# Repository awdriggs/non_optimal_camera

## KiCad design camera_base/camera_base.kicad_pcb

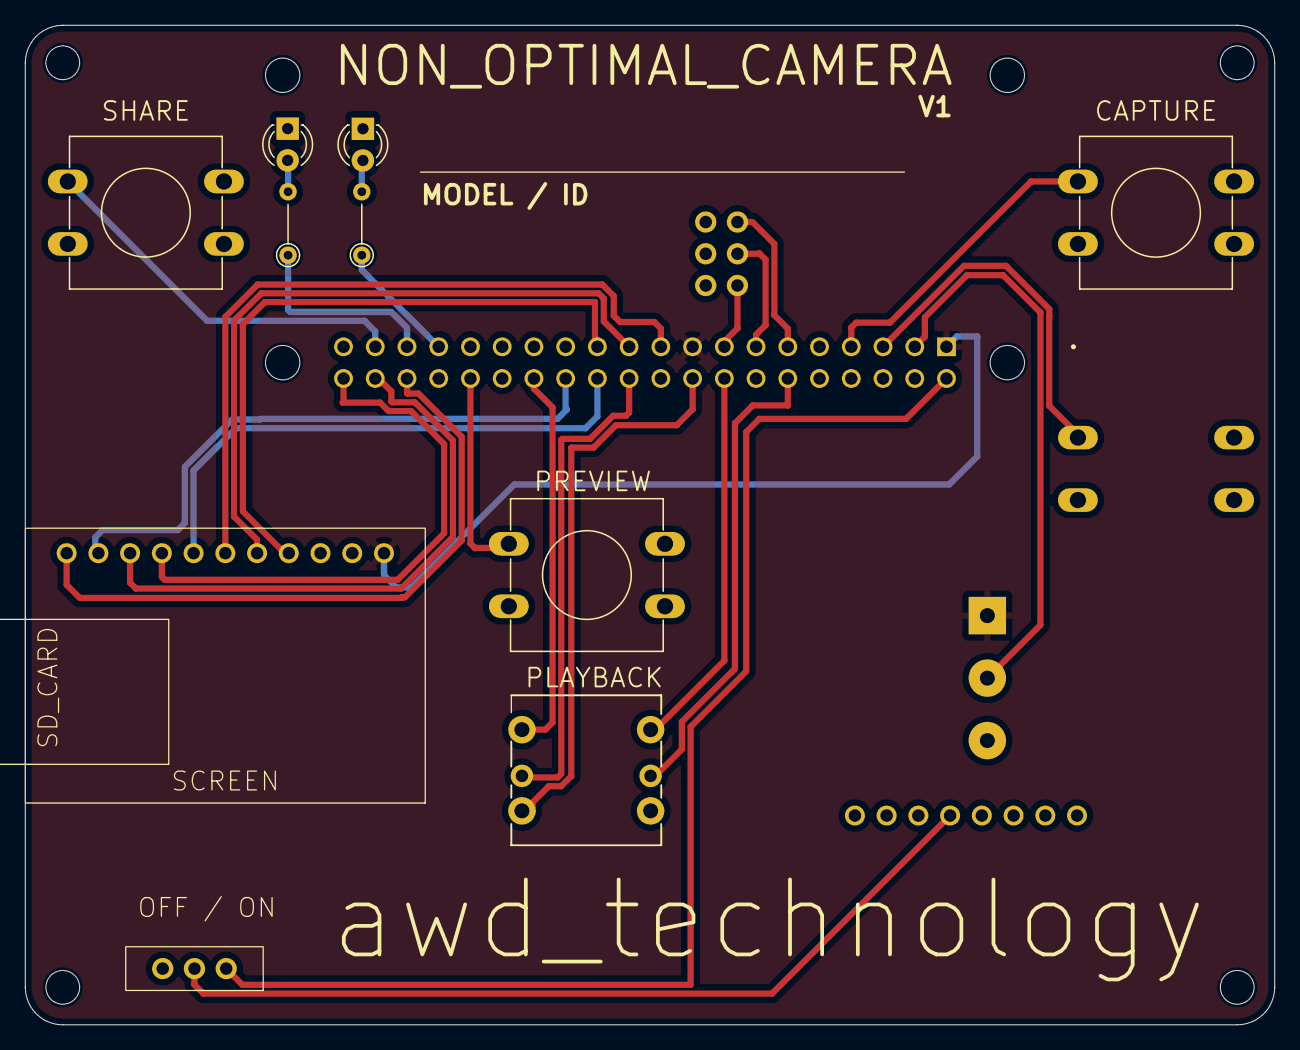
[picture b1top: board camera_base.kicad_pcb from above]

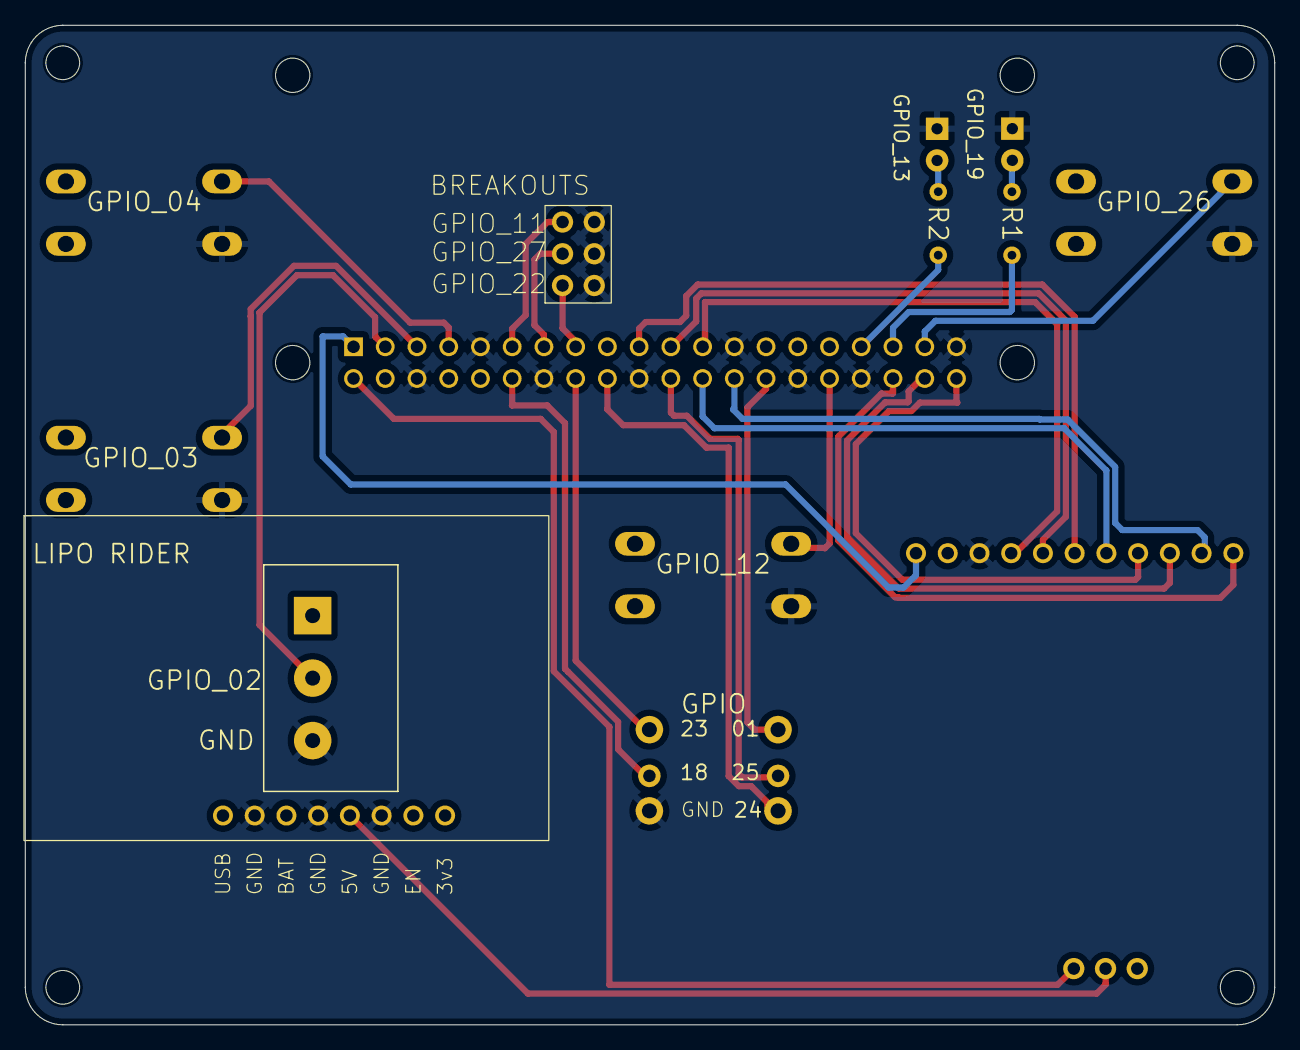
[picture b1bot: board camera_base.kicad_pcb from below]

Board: 2 copper layers, 100.0 x 80.0 mm, 19 parts (2 on the bottom side), 29 nets.

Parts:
D1: GPIO_19; LED_D3.0mm
D2: LED; LED_D3.0mm
H1, H2, H3, H4: MountingHole; MountingHole_2.7mm_M2.5
J1: Raspberry_Pi_4; MODULE_RASPBERRY_PI_ZERO_2_W
J2: Conn_02x03_Odd_Even; PinHeader_2x03_P2.54mm_Vertical
LIPO RIDER: SEED Studio LIPO Rider Plus
R1, R2: R; R_Axial_DIN0204_L3.6mm_D1.6mm_P5.08mm_Vertical
RV1: R_Potentiometer_US; Potentiometer_Alps_RK163_Single_Horizontal
S4: 5D_Button
SCREEN: TFT 1.14
SW1, SW2, SW3, SW5: SW_Push_Dual; PUSH_BUTTON_12mm
U1: switch

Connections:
3v3: J1.1 (3V3), J1.17 (3V3), RV1.1, SCREEN.1 (Vin)
CE0: J1.24 (~CE0_SPI0/GPIO08), SCREEN.7 (TFTCS)
CE1: J1.26 (~CE1_SPI0/GPIO07), SCREEN.10 (SDCS)
GND: D1.1 (K), D2.1 (K), J1.6 (GND), J1.9 (GND), J1.14 (GND), J1.20 (GND), J1.25 (GND), J1.30 (GND), J1.34 (GND), J1.39 (GND), J2.2, J2.4, J2.6, LIPO RIDER.3 (GND), LIPO RIDER.5 (GND), LIPO RIDER.7 (GND), RV1.3, S4.4 (COMMON), SCREEN.3 (GND), SW1.2, SW2.2, SW3.2, SW5.2
GPIO_01: J1.28 (ID_SC_I2C0/GPIO01), S4.1 (A)
GPIO_02: J1.3 (SDA_I2C1/GPIO02), RV1.2
GPIO_03: J1.5 (SCL_I2C1/GPIO03), SW3.1
GPIO_04: J1.7 (GPCLK0/GPIO04), SW2.1
GPIO_11: J1.11 (GPIO17/SPI1_~CE1), J2.5
GPIO_12: J1.32 (GPIO12/PWM0), SW1.1
GPIO_13: J1.33 (GPIO13/PWM1), R2.1
GPIO_16: J1.36 (GPIO16/SPI1_~CE2), SCREEN.11 (LIT)
GPIO_18: J1.12 (GPIO18/SPI1_~CE0/PCM_CLK/PWM0), S4.5 (D)
GPIO_19: J1.35 (GPIO19/SPI1_MISO/PCM_FS), R1.1
GPIO_20: J1.38 (GPIO20/SPI1_MOSI/PCM_DIN/PWM1), SCREEN.9 (DC)
GPIO_21: J1.40 (GPIO21/SPI1_SCLK/PCM_DOUT), SCREEN.8 (RST)
GPIO_22: J1.15 (GPIO22/SDIO_CLK), J2.1
GPIO_23: J1.16 (GPIO23/SDIO_CMD), S4.6 (CENTER)
GPIO_24: J1.18 (GPIO24/SDIO_DAT0), S4.3 (C)
GPIO_25: J1.22 (GPIO25/SDIO_DAT1), S4.2 (B)
GPIO_26: J1.37 (GPIO26/SDIO_DAT2), SW5.1
GPIO_27: J1.13 (GPIO27/SDIO_DAT3), J2.3
MISO: J1.21 (MISO_SPI0/GPIO09), SCREEN.5 (MISO)
MOSI: J1.19 (MOSI_SPI0/GPIO10), SCREEN.6 (MOSI)
unnamed: D1.2 (A), R1.2
unnamed: D2.2 (A), R2.2
unnamed: LIPO RIDER.4 (5V), U1.2 (Vnn)
unnamed: J1.2 (5V), U1.3 (NO)
SCLK: J1.23 (SCLK_SPI0/GPIO11), SCREEN.4 (SCK)

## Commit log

2025-04-22 cable and plexi housing
2025-04-22 2 layer fpc with vias
2025-04-22 aesthetics
2025-04-23 cable sent
2025-04-30 push before cable fix
2025-05-01 fixed and reordered
2025-05-02 testing plexi
